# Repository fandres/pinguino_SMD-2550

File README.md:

This repository is possibly outdated
Este Repositorio se probablemente se encuentra desactualizado

Repository migrated to https://gitlab.com/fandres323/pinguino_SMD-2550
Repositorio migrado a https://gitlab.com/fandres323/pinguino_SMD-2550

# Pinguino SMD 2550

PCB in surface mount of the Pinguino board based on the microcontroller PIC18F2550 

## BOM 

Ref | Qty | Value | Footprint | Package
----- | ---------- | -------- | -------- | --------
C3 | 1| 220nF| Capacitors_SMD:C_1206 | 1206
C1 C2 | 2| 22pF| Capacitors_SMD:C_1206 | 1206
C4 | 1| 100nF| Capacitors_SMD:C_1206 | 1206
C5 | 1| 10uF a 100uF| Capacitors_SMD:c_elec_6.3x5.3 | Capa-e 6x5
D1 | 1| Run LED| LEDs:LED_0805 | 0805
D2 | 1| Power LED| LEDs:LED_0805 | 0805
P1 | 1| USB_OTG| Connect:USB_Mini-B | USB Female mini B 
P2 P3| 1| CONN_01X08| Socket_Strips:Socket_Strip_Straight_1x08 | SIL 1x10 Female
P4 | 1| CONN_01X10| Socket_Strips:Socket_Strip_Straight_1x10 | SIL 1x10 Female
P5 P6 | 1| CONN_01X02| Socket_Strips:Socket_Strip_Straight_1x02 | SIL 1x02 Female
R1 R3 | 2| 470| Resistors_SMD:R_1206 | 1206
R2 | 1| 10k| Resistors_SMD:R_1206 | 1206
SW1 | 1| SW Reset| Buttons_Switches_SMD:SW_SPST_EVQPE1 | SMD Sw 1181
U***1 | 1| PIC18F2550| SMD_Packages:SOJ-28-W | SOP28
Y1 | 1| 22Mhz| Crystal SMD:Crystal_SMD_5032_2Pads | 5032 2pads

<a href="https://oshpark.com/shared_projects/N5pZkoHF"></img></a>

# Pinguino IDE
http://pinguino.cc/download.php

# Images

# Attributions
<br /><span xmlns:dct="http://purl.org/dc/terms/" property="dct:title">Pinguino_SMD-2550</span> por <a xmlns:cc="http://creativecommons.org/ns#" href="https://github.com/fandres/pinguino_SMD-2550" property="cc:attributionName" rel="cc:attributionURL">Fabian Salamanca (fandres)</a> se distribuye bajo una <a rel="license" href="http://creativecommons.org/licenses/by-sa/4.0/">Licencia Creative Commons Atribución-CompartirIgual 4.0 Internacional</a>.<br />Basada en una obra en <a xmlns:dct="http://purl.org/dc/terms/" href="http://www.pinguino.cc/" rel="dct:source">http://www.pinguino.cc/</a>.

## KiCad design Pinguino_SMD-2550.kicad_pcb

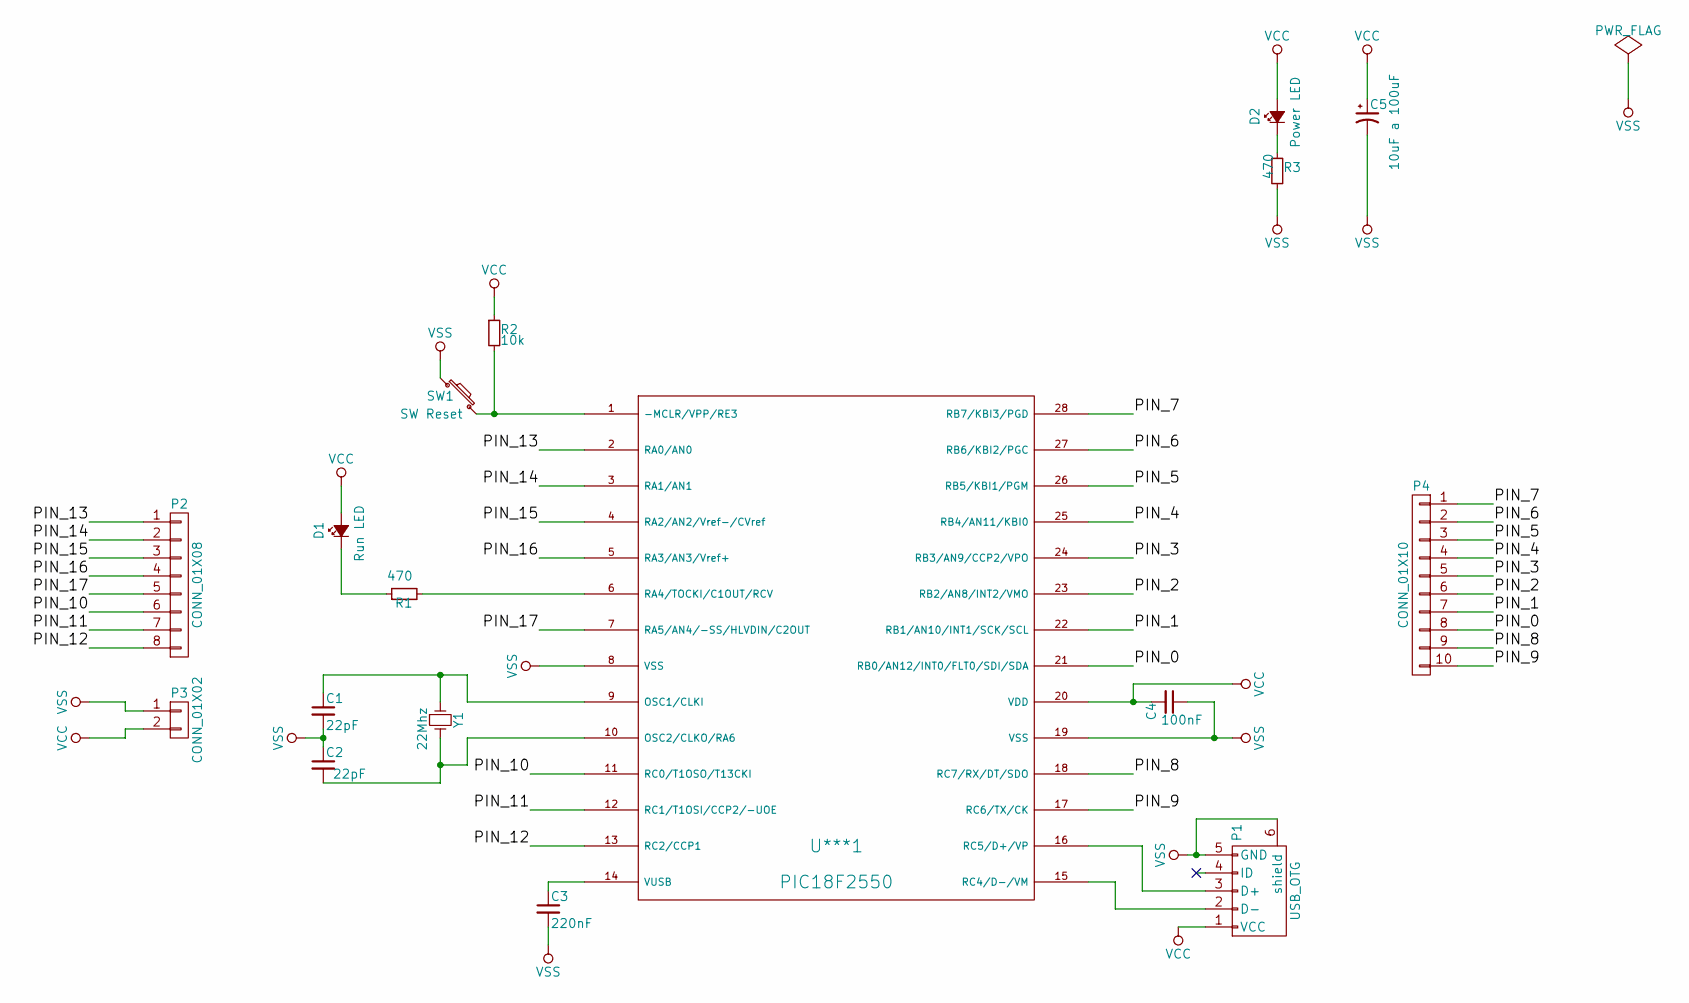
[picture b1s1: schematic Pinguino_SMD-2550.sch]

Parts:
C1, C2: 22pF; C_1206
C3: 220nF; C_1206
C4: 100nF; C_1206
C5: 10uF a 100uF; c_elec_6.3x5.3
D1: Run LED; LED_0805
D2: Power LED; LED_0805
P1: USB_OTG; USB_Mini-B
P2: CONN_01X08; Socket_Strip_Straight_1x08
P3: CONN_01X02; Socket_Strip_Straight_1x02
P4: CONN_01X10; Socket_Strip_Straight_1x10
R1, R3: 470; R_1206
R2: 10k; R_1206
SW1: SW Reset; SW_SPST_EVQPE1
U***1: PIC18F2550; SOJ-28-W
Y1: 22Mhz; Crystal_SMD_5032_2Pads

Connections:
/PIN_0: P4.8, U***1.21 (RB0/AN12/INT0/FLT0/SDI/SDA)
/PIN_1: P4.7, U***1.22 (RB1/AN10/INT1/SCK/SCL)
/PIN_2: P4.6, U***1.23 (RB2/AN8/INT2/VMO)
/PIN_3: P4.5, U***1.24 (RB3/AN9/CCP2/VPO)
/PIN_4: P4.4, U***1.25 (RB4/AN11/KBI0)
/PIN_5: P4.3, U***1.26 (RB5/KBI1/PGM)
/PIN_6: P4.2, U***1.27 (RB6/KBI2/PGC)
/PIN_7: P4.1, U***1.28 (RB7/KBI3/PGD)
/PIN_8: P4.9, U***1.18 (RC7/RX/DT/SDO)
/PIN_9: P4.10, U***1.17 (RC6/TX/CK)
/PIN_10: P2.6, U***1.11 (RC0/T1OSO/T13CKI)
/PIN_11: P2.7, U***1.12 (RC1/T1OSI/CCP2/-UOE)
/PIN_12: P2.8, U***1.13 (RC2/CCP1)
/PIN_13: P2.1, U***1.2 (RA0/AN0)
/PIN_14: P2.2, U***1.3 (RA1/AN1)
/PIN_15: P2.3, U***1.4 (RA2/AN2/Vref-/CVref)
/PIN_16: P2.4, U***1.5 (RA3/AN3/Vref+)
/PIN_17: P2.5, U***1.7 (RA5/AN4/-SS/HLVDIN/C2OUT)
unnamed: C1.1, U***1.9 (OSC1/CLKI), Y1.1
unnamed: C2.2, U***1.10 (OSC2/CLKO/RA6), Y1.2
unnamed: C3.1, U***1.14 (VUSB)
unnamed: D1.1 (K), R1.1
unnamed: D2.1 (K), R3.1
unnamed: P1.2 (D-), U***1.15 (RC4/D-/VM)
unnamed: P1.3 (D+), U***1.16 (RC5/D+/VP)
unnamed: R1.2, U***1.6 (RA4/TOCKI/C1OUT/RCV)
unnamed: R2.2, SW1.2, U***1.1 (-MCLR/VPP/RE3)
VCC: C4.2, C5.1, D1.2 (A), D2.2 (A), P1.1 (VCC), P3.2, R2.1, U***1.20 (VDD)
VSS: C1.2, C2.1, C3.2, C4.1, C5.2, P1.5 (GND), P1.6 (shield), P3.1, R3.2, SW1.1, U***1.8 (VSS), U***1.19 (VSS)

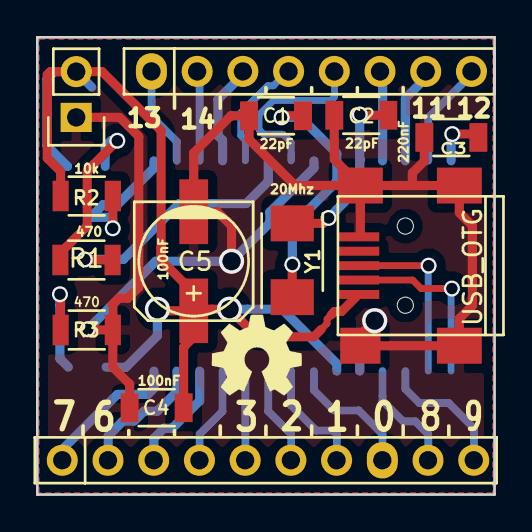
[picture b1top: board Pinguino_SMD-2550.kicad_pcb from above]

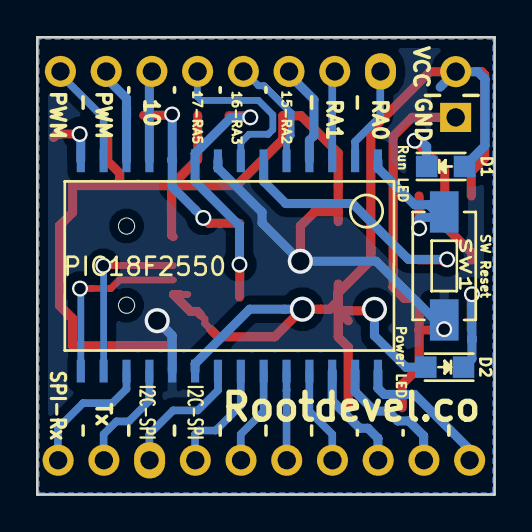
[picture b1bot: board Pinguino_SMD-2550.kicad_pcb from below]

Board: 2 copper layers, 25.4 x 25.4 mm, 17 parts (4 on the bottom side), 29 nets.

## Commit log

2016-12-21 REV:1B
2016-12-22 Upload project -REV1B
2016-12-27 Modelo en 3D de la targeta, asi como de la cubierta
2016-12-27 Modify README.md file, updated BOM and add OSHW logo in SS layer.
2016-12-27 Added images
2017-01-03 Update info: BOM and README
2017-01-05 Bug Fixed: Footprint USB Micro B
2017-02-04 F. SilkS
2017-02-21 The Silkscreen has been corrected and the new PCBs have been generated (Gerber and PDF)
2017-02-21 Modified readme.md file. Add Licence
2017-02-21 Modified readme.md file
2017-02-22 Fixed
2018-06-12 Update README.md
    Repository migrated to https://gitlab.com/fandres323/pinguino_SMD-2550
